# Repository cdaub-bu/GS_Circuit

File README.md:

# GS_Circuit

LED night-light for GSA activity

## Notes from aftermath of 2026

### Hardware

* Light sensor wired incorrectly:
  <br>Emitter should go to GND
  <br>Collector should go through resistor to VCC
* Light sensor needs to go to an ADC pin.  This is tricky as there are so few pins.
  
Here is the table of ATTiny85 pins:

|            Other | GPIO | # | # | GPIO | Other           |
|-----------------:|------|---|:--|------|-----------------|
| nRST/<b>ADC0</b> | PB5  | 1 | 8 |      | VCC             |
|      <b>ADC3</b> | PB3  | 2 | 7 | PB2  | SCK/<b>ADC1</b> |
|      <b>ADC2</b> | PB4  | 3 | 6 | PB1  | MISO            |
|              GND |      | 4 | 5 | PB0  | MOSI            |
|                  |      |   |   |      |                 |

We need to avoid pins 5, 6, 7 and 1 if we want to use ISP.
<br>That leaves 2, 3 as ADC pins.  Those are used for LEDs to avoid conflict with the ISP.
<br>So no obvious solution, as the LEDs and light sensor cannot share pins with the ISP.

Propose to add 1 or 2 BS170 MOSFETs to drive the LEDs.  Then these
pins can share the ISP pins with no problem.

See below for proposed circuit changes.  One might want a pull-down
on the MOSFET gate(s).

<p>

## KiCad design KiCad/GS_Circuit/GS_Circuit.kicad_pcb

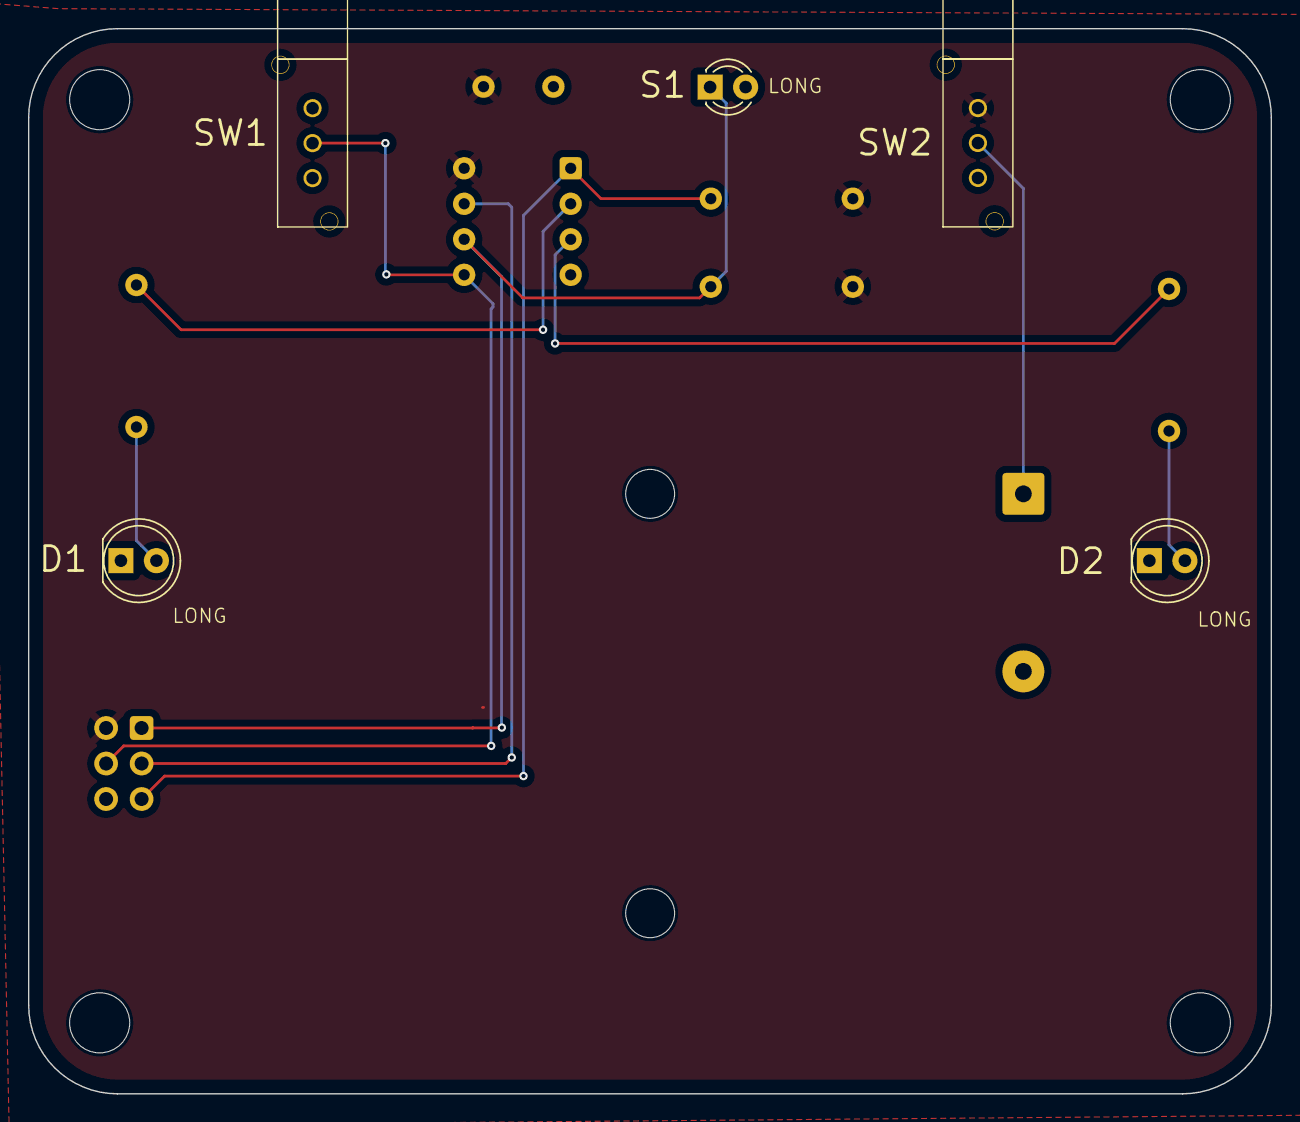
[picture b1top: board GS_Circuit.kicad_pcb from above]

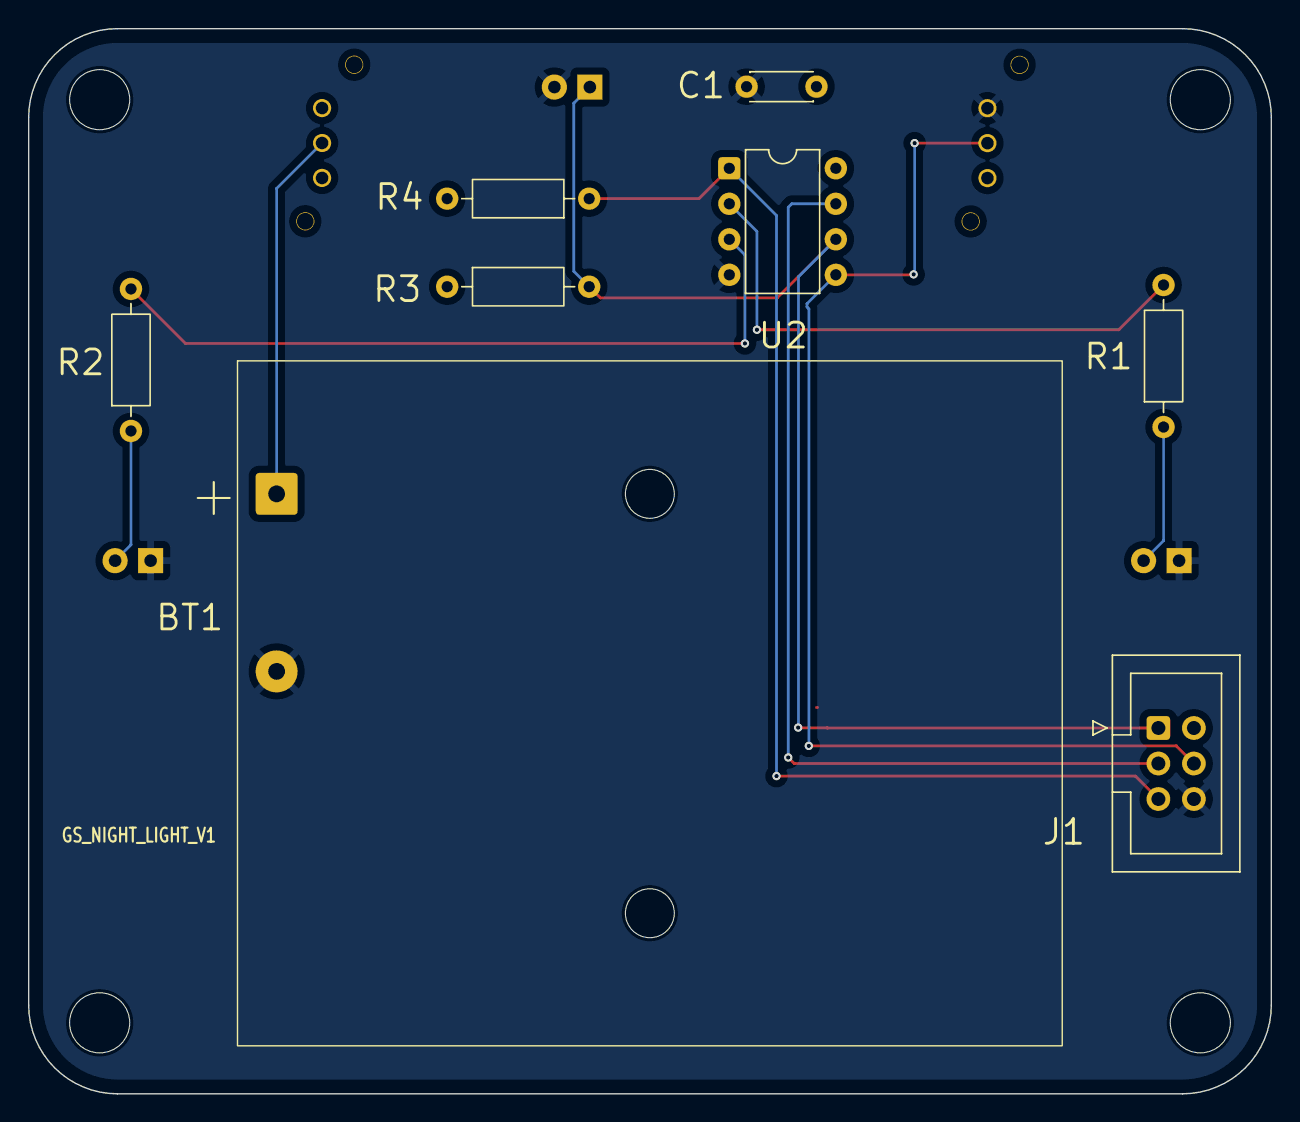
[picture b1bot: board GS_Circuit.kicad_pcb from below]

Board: 2 copper layers, 88.9 x 76.2 mm, 17 parts (8 on the bottom side), 11 nets.

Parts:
BT1: Battery; BatteryHolder_Keystone_2464
C1: .1 uf; C_Disc_D4.3mm_W1.9mm_P5.00mm
D1, D2: LED, QBL8XX60Y Series; LED_D5.0mm
H1, H2, H3, H4: MountingHole; MountingHole_4.3mm_M4
J1: AVR-ISP-6; IDC-Header_2x03_P2.54mm_Vertical
R1, R2: 91 Ohms; R_Axial_DIN0207_L6.3mm_D2.5mm_P10.16mm_Horizontal
R3: 10K; R_Axial_DIN0207_L6.3mm_D2.5mm_P10.16mm_Horizontal
R4: R_US; R_Axial_DIN0207_L6.3mm_D2.5mm_P10.16mm_Horizontal
S1: TEPT 4400; THT_TEPT4400
SW1: SW_Push; LC 1258
SW2: SW_SPST; LC 1258
U2: ATtiny85V-10P; DIP-8_W7.62mm

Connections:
/MISO: J1.1 (MISO), R3.2, S1.1 (K), U2.6 (PB1)
/MOSI: J1.4 (MOSI), SW1.1, U2.5 (AREF/PB0)
/SCK: J1.3 (SCK), U2.7 (PB2)
/~RST: J1.5 (~RST), R4.1, U2.1 (~RESET/PB5)
GND: BT1.2 (-), C1.2, D1.1 (K), D2.1 (K), J1.6 (GND), S1.2 (A), SW1.2, U2.4 (GND)
unnamed: BT1.1 (+), SW2.1 (A)
unnamed: D1.2 (A), R1.1
unnamed: D2.2 (A), R2.1
unnamed: R1.2, U2.2 (XTAL1/PB3)
unnamed: R2.2, U2.3 (XTAL2/PB4)
VCC: C1.1, J1.2 (VCC), R3.1, R4.2, SW2.2 (B), U2.8 (VCC)

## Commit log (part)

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2026-01-15 Initial Circuit Files
2026-01-16 Foot Print and Componentry
    First Try at foot print.
    LEDs are sourced
    Need help on switches.
2026-01-17 First try foot print
    Added library components with foot prints. (photo sensor and switches).
    First draft at PCB layout.
2026-01-18 MD Electron Feedback 1
    -Changed Library Structure
    -Fixed switch footprint issue
    -Added PCB over all footprint and layout
    -Moved silkscreen labels
    -
2026-01-18 Initialize README with project details
    Add project title and description to README
2026-01-19 Fixed Battery Layout
2026-01-19 MD e-negative feedback 2
    - Moved capacitor & rotate
    - Updated foot prints for LEDS
    - Added BOM
2026-01-19 Loose Saves
2026-01-19 MD E Feeback 3
    Moved Lights
    Horizontal/Vertical Wiring
2026-01-20 Wiring
2026-01-20 Moved lights to border
2026-01-20 Fixed Connecions for LEDS
2026-01-20 Rev 1 as built
2026-01-28 starting on software
2026-01-28 readme
2026-01-28 working on reducing the sleep power
2026-01-30 working on software
2026-02-01 Rev 1 PCB, working on software
2026-02-04 working on light sensor
2026-02-09 sensor test
2026-02-10 work on software
2026-02-10 simple working version no pin change wakeup 0.5uA
2026-02-11 First release with 45m timeout
2026-02-11 final tweaks
2026-02-12 move old software to Testing
